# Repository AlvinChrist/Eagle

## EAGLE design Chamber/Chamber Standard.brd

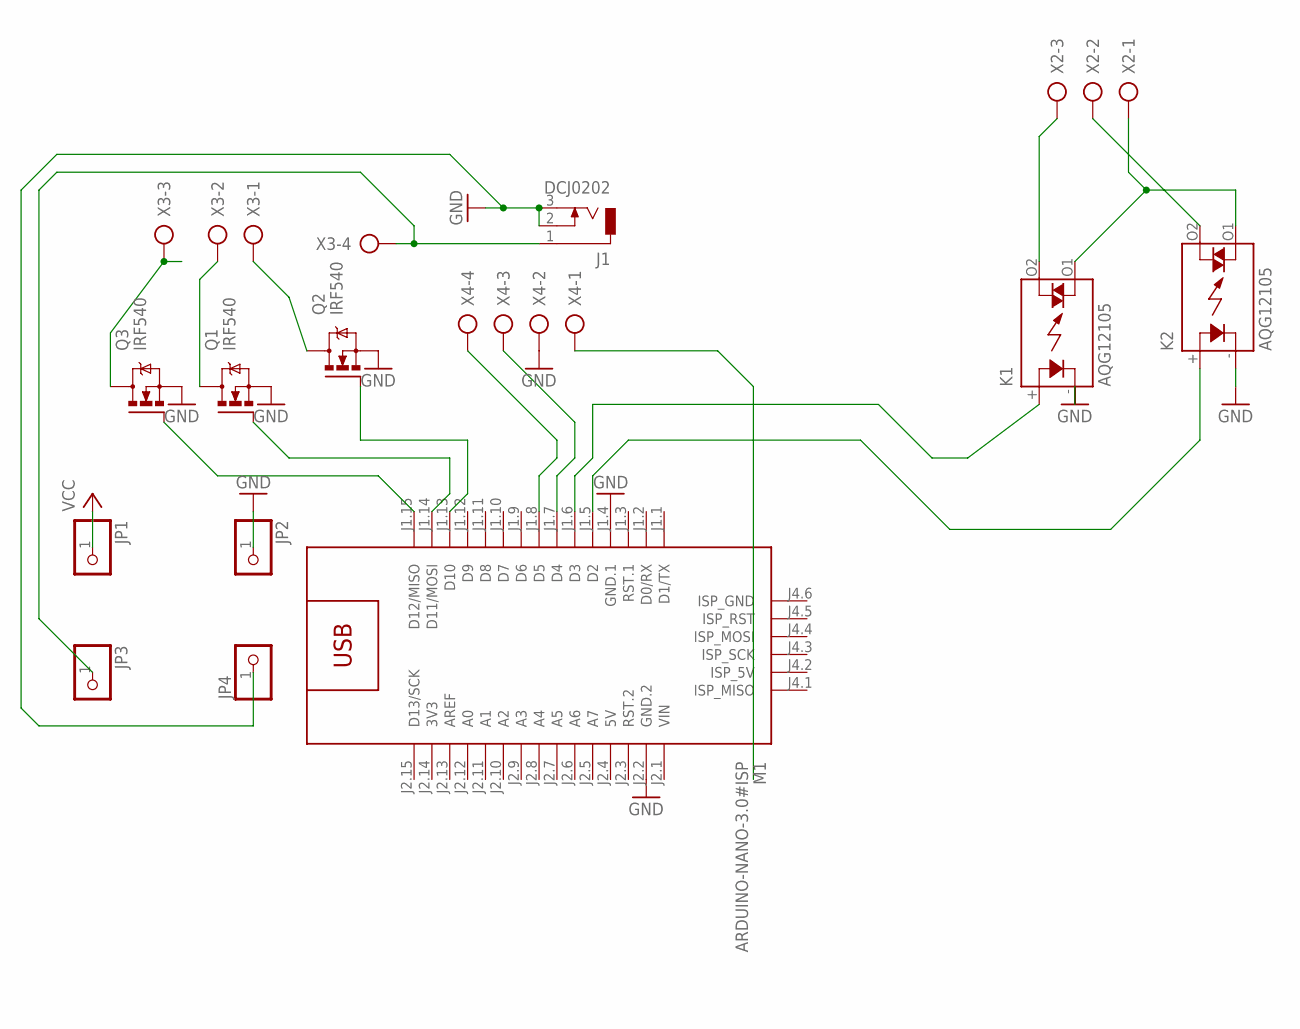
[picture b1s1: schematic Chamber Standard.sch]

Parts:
J1: DCJ0202
JP1, JP2, JP3, JP4: PINHD-1X1; 1X01
K1, K2: AQG12105; AQG
M1: ARDUINO-NANO-3.0#ISP
Q1, Q2, Q3: IRF540; TO220BV
X2: AK300/3
X3, X4: AK300/4

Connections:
3V3: M1.J2.14 (3V3)
5V: M1.J2.4 (5V), X4.1
12V: J1.1, JP3.1, X3.4
GND: J1.2, J1.3, JP2.1, JP4.1, K1.- (K), K2.- (K), Q1.S, Q2.S, Q3.S, X4.2
GND.1: M1.J2.2 (GND.2)
GND.2: M1.J1.4 (GND.1)
unnamed: M1.J1.13 (D10), Q2.G
unnamed: M1.J1.15 (D12/MISO), Q3.G
unnamed: K2.O2 (DS1), X2.2
unnamed: Q3.D, X3.3
unnamed: Q1.D, X3.2
unnamed: Q2.D, X3.1
unnamed: K1.+ (A), M1.J1.6 (D3)
unnamed: K2.+ (A), M1.J1.5 (D2)
unnamed: K1.O1 (DS2), K2.O1 (DS2), X2.1
unnamed: K1.O2 (DS1), X2.3
unnamed: M1.J1.7 (D4), X4.3
unnamed: M1.J1.8 (D5), X4.4
unnamed: M1.J1.14 (D11/MOSI), Q1.G
VCC: JP1.1
VIN: M1.J2.1 (VIN)

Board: 2 copper layers, 14 parts (0 on the bottom side), 16 nets, no tracks yet.

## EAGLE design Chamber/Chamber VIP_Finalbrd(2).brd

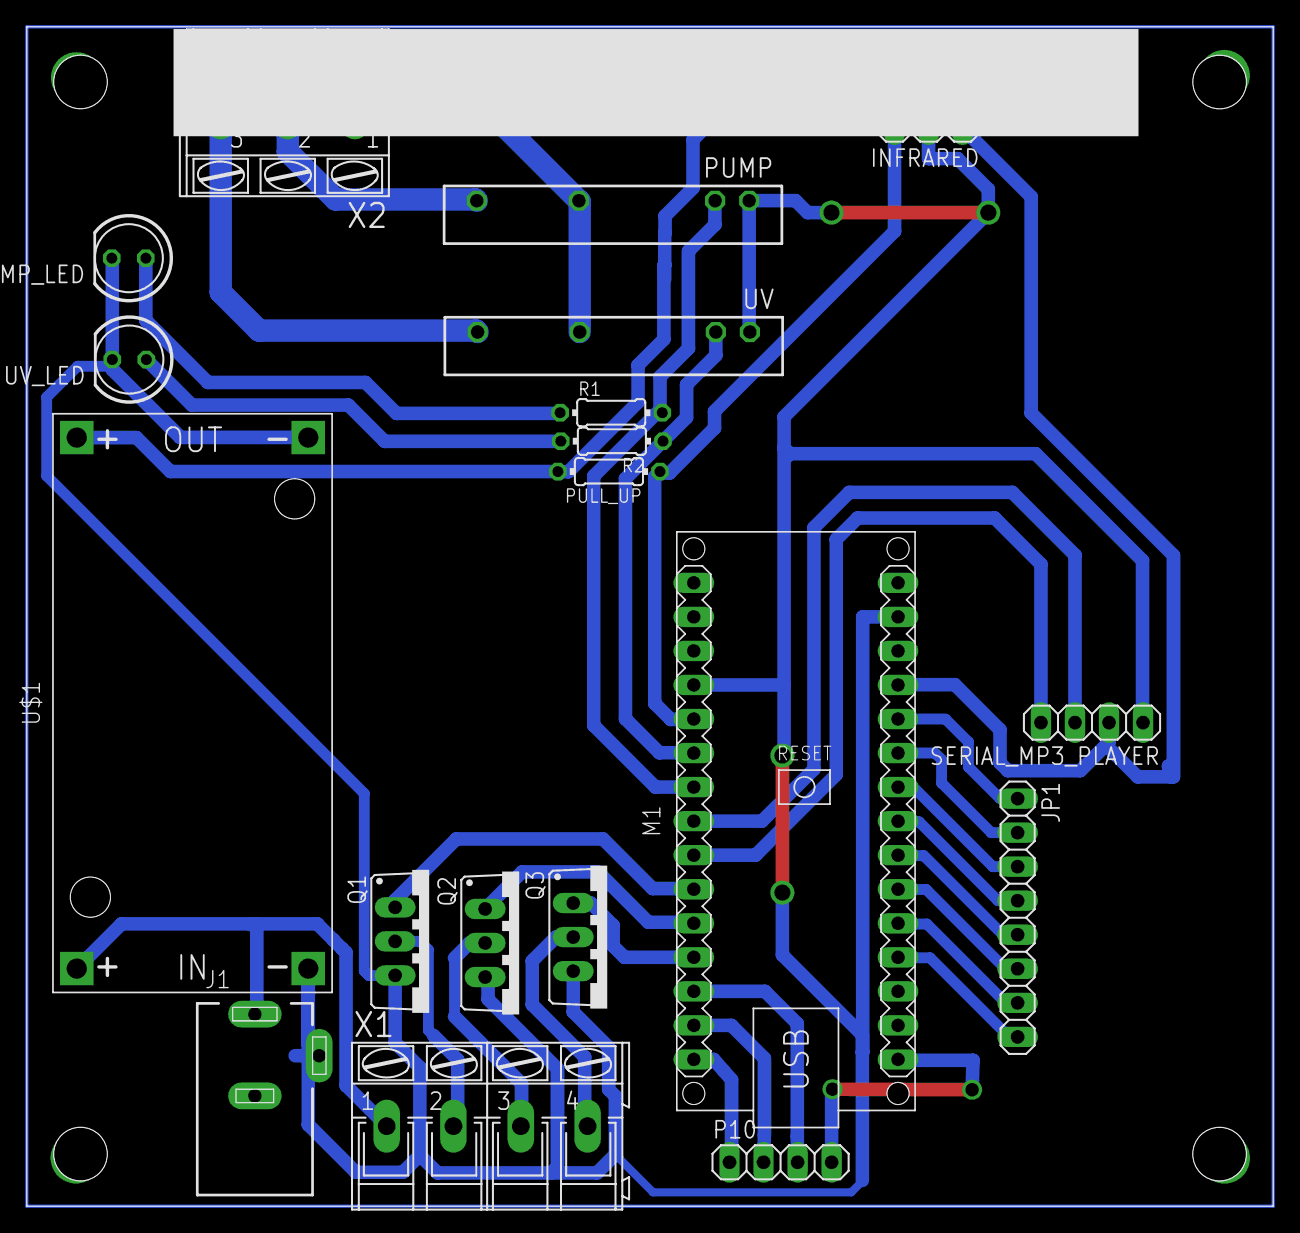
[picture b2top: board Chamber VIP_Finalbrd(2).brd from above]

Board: 2 copper layers, 93.0 x 88.0 mm, 19 parts (0 on the bottom side), 31 nets.

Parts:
INFRARED: 1X03
J1: DCJ0202
JP1: 1X08
M1: ARDUINO-NANO-3.0#ISP; ARDUINO-NANO-3.0
P10: 1X04
PULL_UP: 10k ohm; 0204/7
PUMP: AQG12105; AQG
PUMP_LED: LED5MM
Q1, Q2, Q3: IRF540; TO220BV
R1, R2: 1k ohm; 0204/7
SERIAL_MP3_PLAYER: 1X04
U$1: DC-DC-STEP-DOWN-LM2596
UV: AQG12105; AQG
UV_LED: LED5MM
X1: AK300/4
X2: AK300/3

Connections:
+5V: INFRARED.1, M1.J2.4, PULL_UP.2, SERIAL_MP3_PLAYER.2, U$1.OUT+
GND: INFRARED.2, J1.2, J1.3, M1.J1.4, M1.J2.2, PUMP.-, PUMP_LED.K, Q1.S, Q2.S, Q3.S, SERIAL_MP3_PLAYER.1, U$1.IN-, U$1.OUT-, UV.-, UV_LED.K
unnamed: Q3.D, X1.4
unnamed: J1.1, U$1.IN+, X1.1
unnamed: Q1.D, X1.2
unnamed: Q2.D, X1.3
unnamed: JP1.8, M1.J2.12
unnamed: PUMP.O2, X2.2
unnamed: M1.J1.12, Q3.G
unnamed: M1.J1.6, R2.1, UV.+
unnamed: M1.J1.10, Q1.G
unnamed: M1.J1.11, Q2.G
unnamed: M1.J1.9, SERIAL_MP3_PLAYER.4
unnamed: INFRARED.3, M1.J1.5, PULL_UP.1
unnamed: R2.2, UV_LED.A
unnamed: PUMP_LED.A, R1.1
unnamed: M1.J1.8, SERIAL_MP3_PLAYER.3
unnamed: M1.J1.7, PUMP.+, R1.2
unnamed: M1.J1.15, P10.1
unnamed: M1.J1.14, P10.2
unnamed: M1.J1.13, P10.3
unnamed: M1.J2.15, P10.4
unnamed: UV.O2, X2.3
unnamed: JP1.7, M1.J2.11
unnamed: JP1.6, M1.J2.10
unnamed: JP1.5, M1.J2.9
unnamed: JP1.4, M1.J2.8
unnamed: JP1.3, M1.J2.7
unnamed: JP1.2, M1.J2.6
unnamed: JP1.1, M1.J2.5
S$3: PUMP.O1, UV.O1, X2.1

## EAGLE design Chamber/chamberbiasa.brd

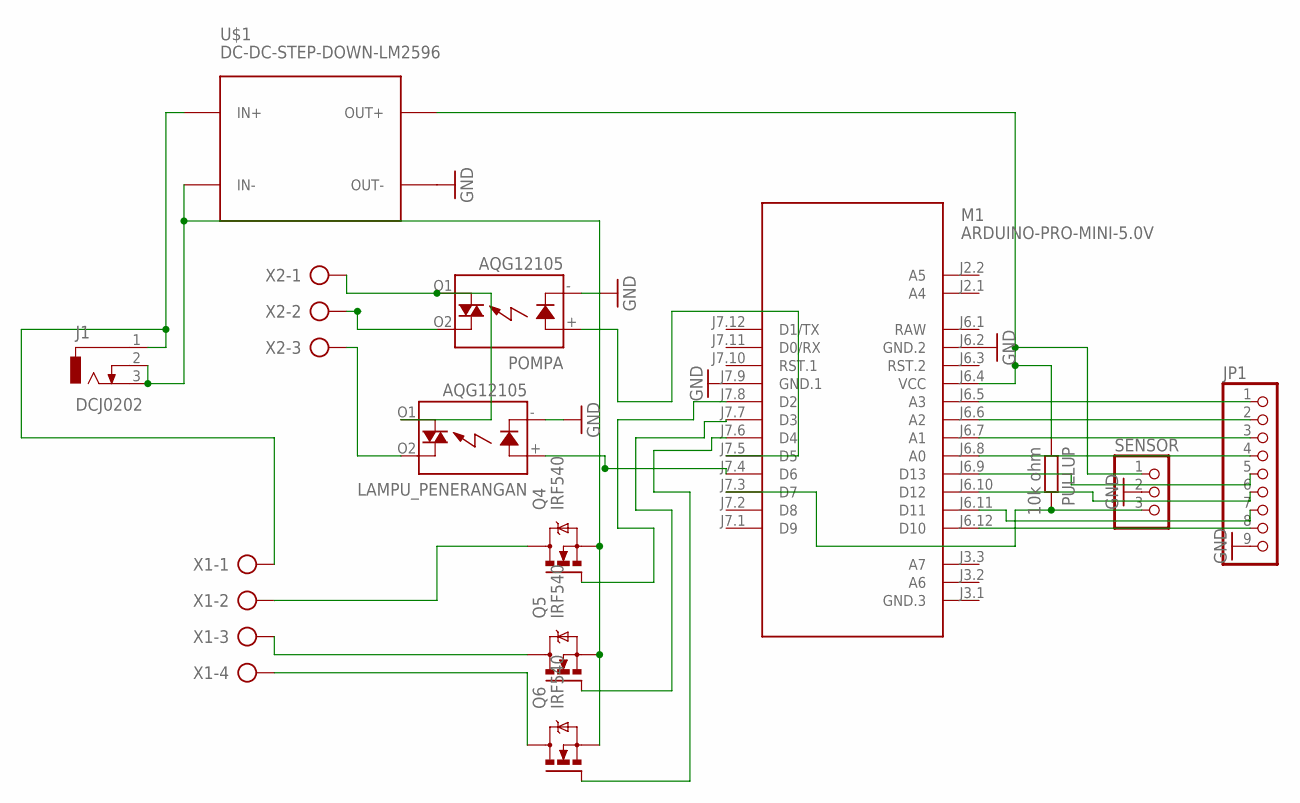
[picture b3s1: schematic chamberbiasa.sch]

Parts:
J1: DCJ0202
JP1: PINHD-1X9; 1X09
LAMPU_PENERANGAN: AQG12105; AQG
M1: ARDUINO-PRO-MINI-5.0V; ARDUINO-PRO-MINI
POMPA: AQG12105; AQG
PULLUP: 10k ohm; 0204/7
Q4, Q5, Q6: IRF540; TO220BV
SENSOR: PINHD-1X3; 1X03
U$1: DC-DC-STEP-DOWN-LM2596
X1: AK300/4
X2: AK300/3

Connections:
5V: M1.J6.4 (VCC), PULLUP.1, SENSOR.1, U$1.OUT+
-12V: J1.2, J1.3, Q4.S, Q5.S, Q6.S, U$1.IN-
GND: JP1.9, LAMPU_PENERANGAN.- (K), M1.J6.2 (GND.2), M1.J7.9 (GND.1), POMPA.- (K), SENSOR.2, U$1.OUT-
unnamed: LAMPU_PENERANGAN.+ (A), M1.J7.4 (D6)
unnamed: M1.J7.8 (D2), Q4.G
unnamed: M1.J7.5 (D5), POMPA.+ (A)
unnamed: M1.J7.7 (D3), Q5.G
unnamed: M1.J7.6 (D4), Q6.G
unnamed: Q4.D, X1.2
unnamed: Q5.D, X1.3
unnamed: Q6.D, X1.4
unnamed: J1.1, U$1.IN+, X1.1
unnamed: POMPA.O2 (DS1), X2.2
unnamed: LAMPU_PENERANGAN.O1 (DS2), POMPA.O1 (DS2), X2.1
unnamed: LAMPU_PENERANGAN.O2 (DS1), X2.3
unnamed: JP1.1, M1.J6.5 (A3)
unnamed: M1.J7.3 (D7), PULLUP.2, SENSOR.3
unnamed: JP1.2, M1.J6.6 (A2)
unnamed: JP1.3, M1.J6.7 (A1)
unnamed: JP1.4, M1.J6.8 (A0)
unnamed: JP1.5, M1.J6.9 (D13)
unnamed: JP1.6, M1.J6.10 (D12)
unnamed: JP1.7, M1.J6.11 (D11)
unnamed: JP1.8, M1.J6.12 (D10)
RAW: M1.J6.1 (RAW)

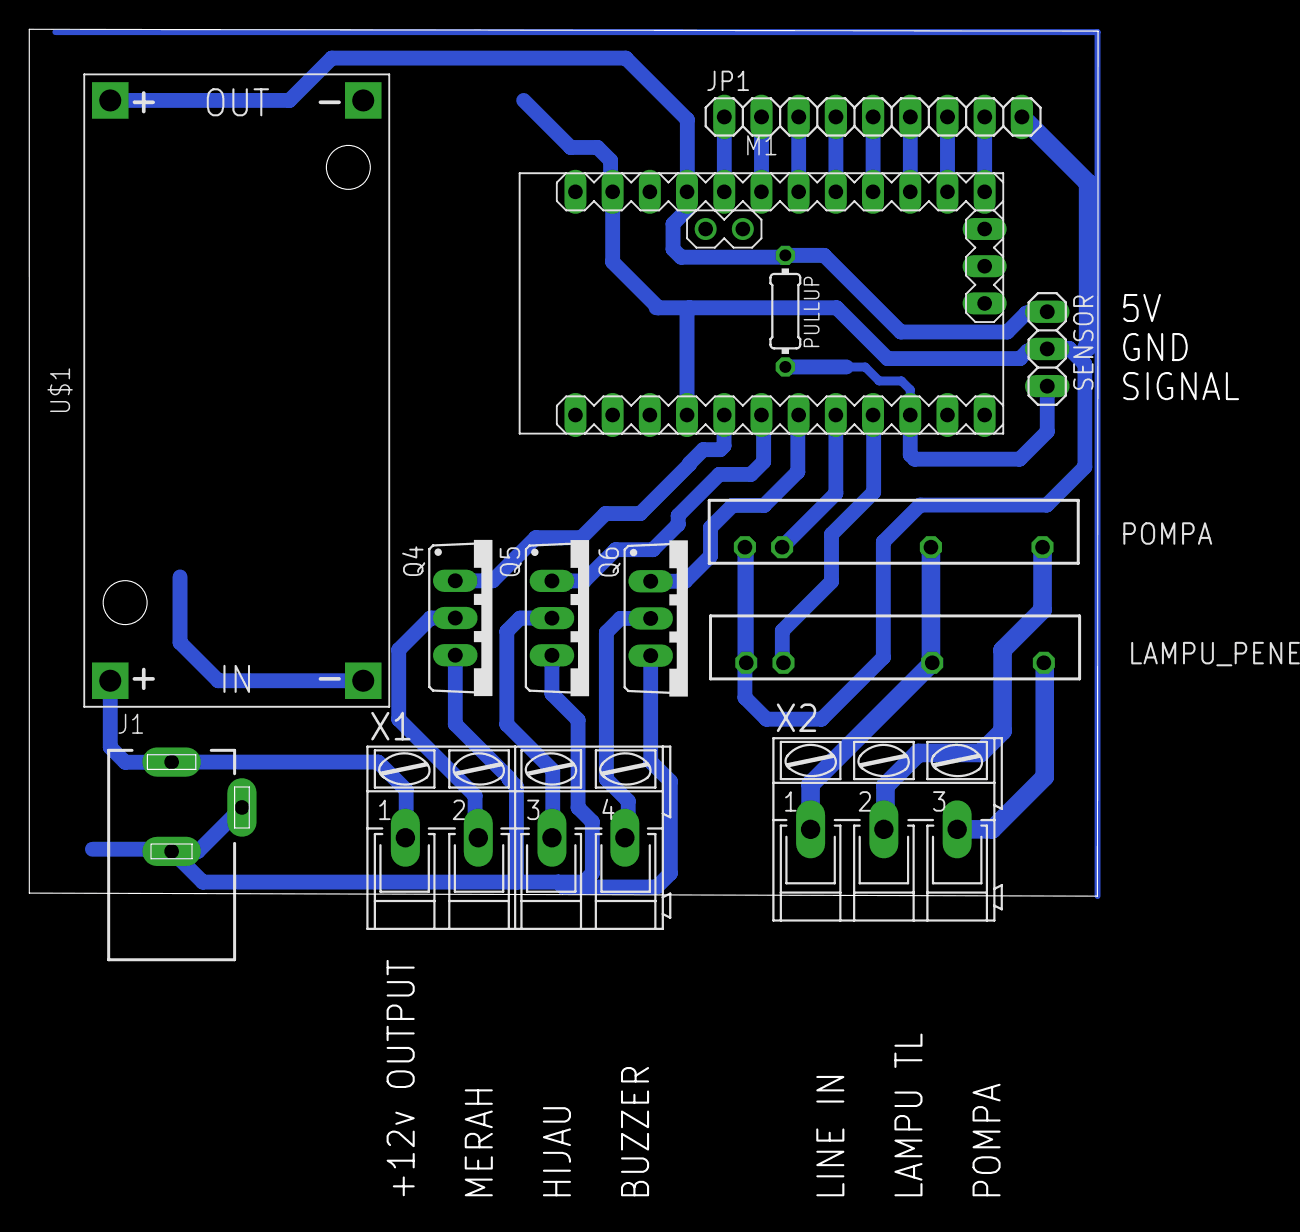
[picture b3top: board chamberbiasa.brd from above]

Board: 2 copper layers, 73.0 x 59.2 mm, 13 parts (0 on the bottom side), 24 nets.

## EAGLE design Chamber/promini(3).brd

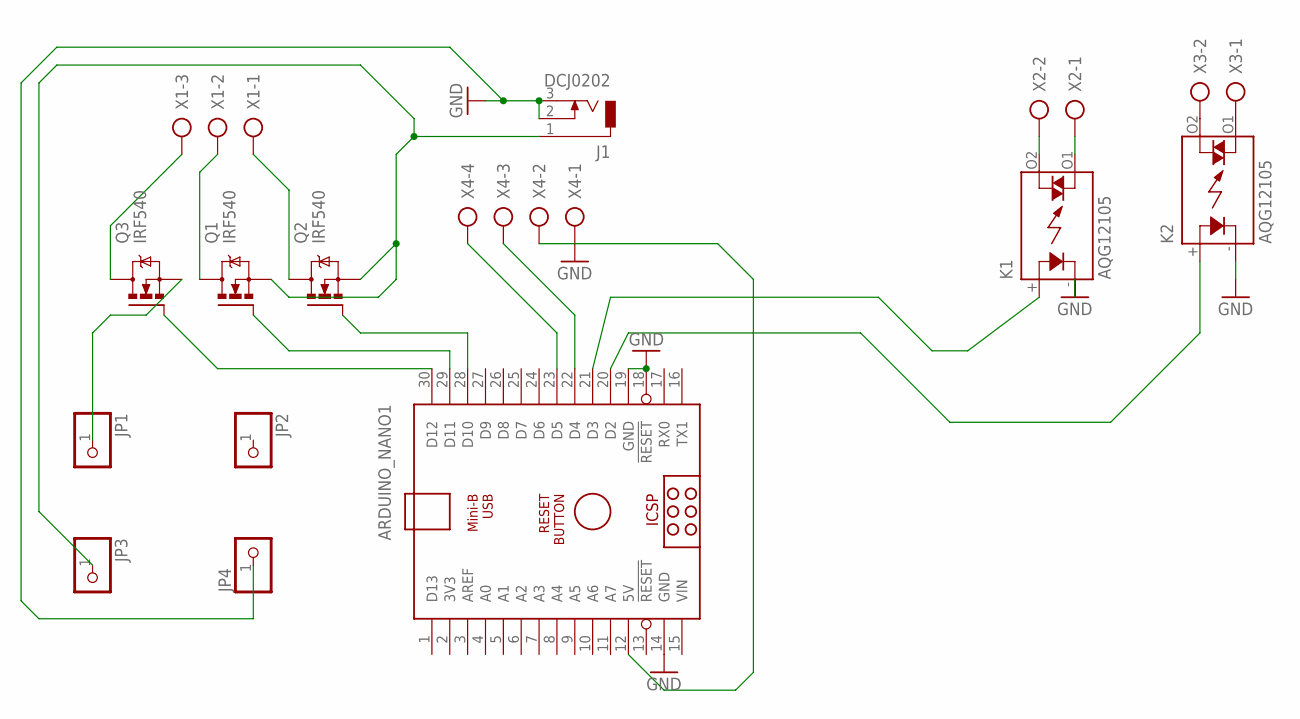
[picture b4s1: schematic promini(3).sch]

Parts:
ARDUINO_NANO1: ARDUINO_NANO
J1: DCJ0202
JP1, JP2, JP3, JP4: PINHD-1X1; 1X01
K1, K2: AQG12105; AQG
Q1, Q2, Q3: IRF540; TO220BV
X1: AK300/3
X2, X3: AK300/2
X4: AK300/4

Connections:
5V: ARDUINO_NANO1.12 (5V), X4.2
12V: J1.1, JP3.1, Q1.S, Q2.S
GND: ARDUINO_NANO1.14 (GND), ARDUINO_NANO1.18 (!RESET), ARDUINO_NANO1.19 (GND), J1.2, J1.3, JP4.1, K1.- (K), K2.- (K), X4.1
unnamed: ARDUINO_NANO1.28 (D10), Q2.G
unnamed: ARDUINO_NANO1.30 (D12), Q3.G
unnamed: JP1.1, Q3.S
unnamed: Q3.D, X1.3
unnamed: Q1.D, X1.2
unnamed: Q2.D, X1.1
unnamed: ARDUINO_NANO1.21 (D3), K1.+ (A)
unnamed: ARDUINO_NANO1.20 (D2), K2.+ (A)
unnamed: K1.O1 (DS2), X2.1
unnamed: K1.O2 (DS1), X2.2
unnamed: K2.O1 (DS2), X3.1
unnamed: K2.O2 (DS1), X3.2
unnamed: ARDUINO_NANO1.22 (D4), X4.3
unnamed: ARDUINO_NANO1.23 (D5), X4.4
unnamed: ARDUINO_NANO1.29 (D11), Q1.G
VIN: ARDUINO_NANO1.15 (VIN)

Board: 2 copper layers, 15 parts (0 on the bottom side), 18 nets, no tracks yet.

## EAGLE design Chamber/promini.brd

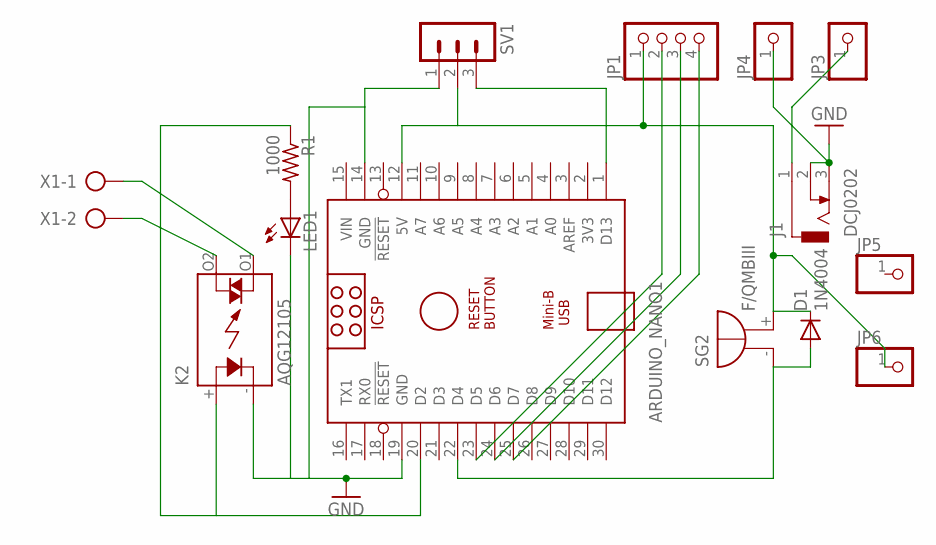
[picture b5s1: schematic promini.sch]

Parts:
ARDUINO_NANO1: ARDUINO_NANO
D1: 1N4004; DO41-10
J1: DCJ0202
JP1: PINHD-1X4; 1X04
JP3, JP4, JP5, JP6: PINHD-1X1; 1X01
K2: AQG12105; AQG
LED1: LED5MM
R1: 1000; 0204/7
SG2: F/QMBIII
SV1: MA03-1
X1: AK300/2

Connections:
5V: ARDUINO_NANO1.12 (5V), D1.C, JP1.1, JP6.1, SG2.+ (-), SV1.2
D2: ARDUINO_NANO1.20 (D2), K2.+ (A), R1.1
D4: ARDUINO_NANO1.22 (D4), D1.A, SG2.- (+)
D13: ARDUINO_NANO1.1 (D13), SV1.3
GND: ARDUINO_NANO1.14 (GND), ARDUINO_NANO1.19 (GND), J1.2, J1.3, JP4.1, K2.- (K), LED1.K (C), SV1.1
unnamed: K2.O2 (DS1), X1.2
unnamed: K2.O1 (DS2), X1.1
unnamed: ARDUINO_NANO1.23 (D5), JP1.2
unnamed: LED1.A, R1.2
unnamed: J1.1, JP3.1
unnamed: ARDUINO_NANO1.24 (D6), JP1.3
unnamed: ARDUINO_NANO1.25 (D7), JP1.4
VIN: ARDUINO_NANO1.15 (VIN)

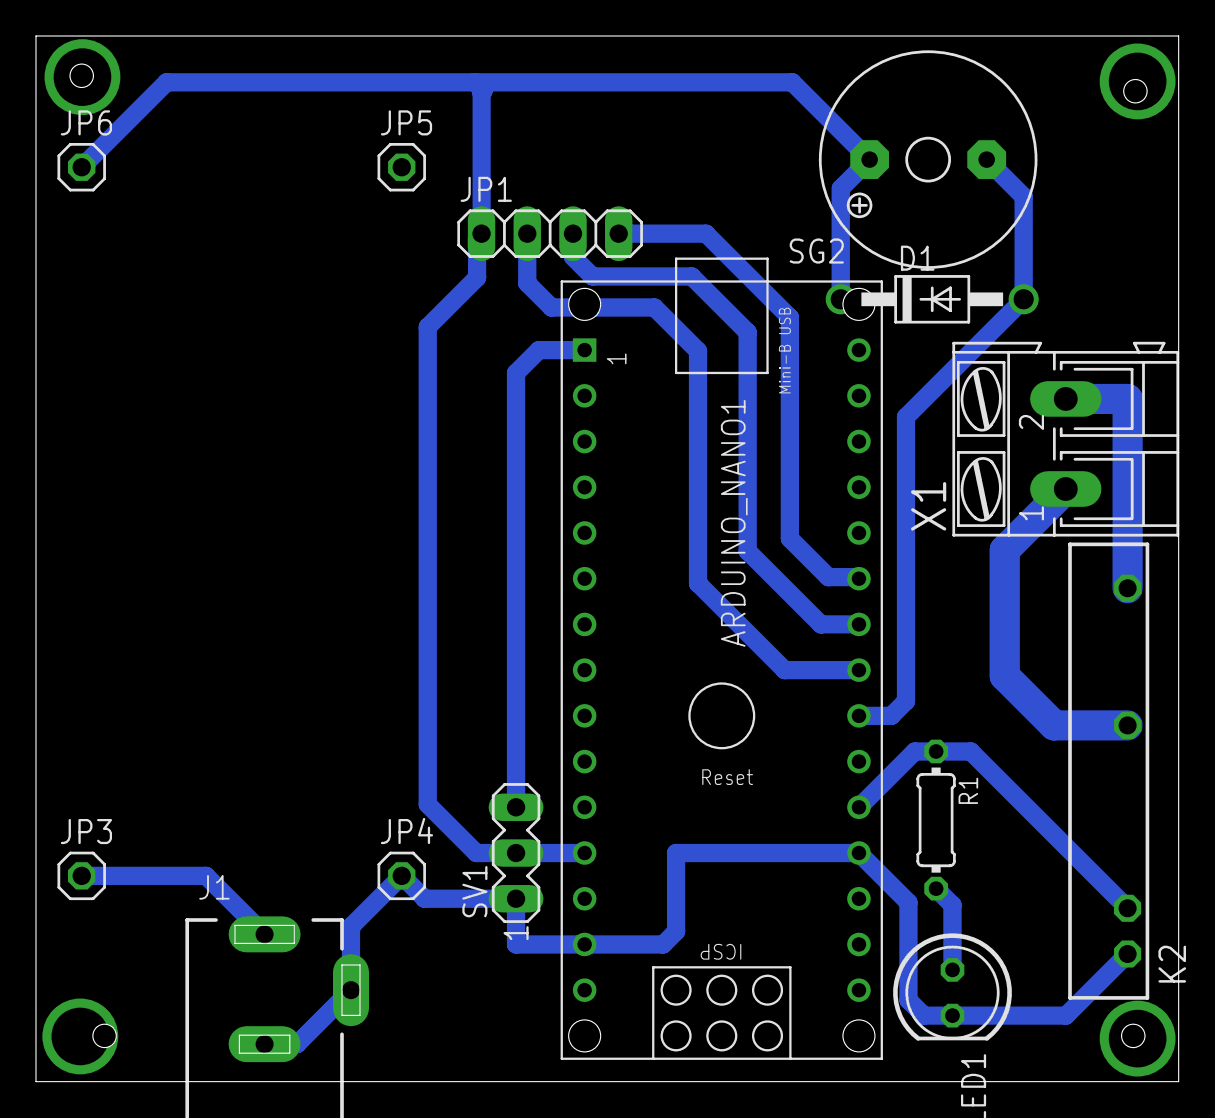
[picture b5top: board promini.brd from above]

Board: 2 copper layers, 63.5 x 58.1 mm, 14 parts (0 on the bottom side), 12 nets.

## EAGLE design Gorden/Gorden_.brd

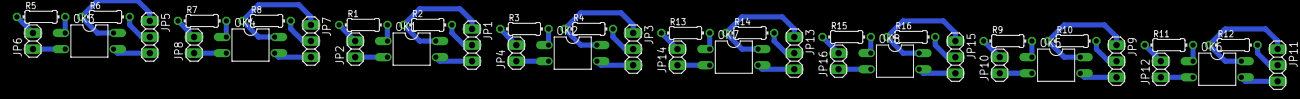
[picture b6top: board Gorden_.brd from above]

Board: 2 copper layers, 40 parts (0 on the bottom side), 48 nets.

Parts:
JP1, JP3, JP5, JP7, JP9, JP11, JP13, JP15: 1X03
JP2, JP4, JP6, JP8, JP10, JP12, JP14, JP16: 1X02
OK1, OK2, OK3, OK4, OK5, OK6, OK7, OK8: PC817; DIL04
R1, R2, R3, R4, R5, R6, R7, R8, R9, R10, R11, R12, R13, R14, R15, R16: 0204/7

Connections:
unnamed: JP1.3, OK1.3
unnamed: OK1.1, R1.2
unnamed: JP1.1, OK1.4, R2.1
unnamed: JP1.2, R2.2
unnamed: JP2.2, R1.1
unnamed: JP2.1, OK1.2
unnamed: OK2.1, R3.2
unnamed: JP3.3, OK2.3
unnamed: JP3.1, OK2.4, R4.1
unnamed: JP3.2, R4.2
unnamed: JP4.2, R3.1
unnamed: JP4.1, OK2.2
unnamed: OK3.1, R5.2
unnamed: JP5.3, OK3.3
unnamed: JP5.1, OK3.4, R6.1
unnamed: JP5.2, R6.2
unnamed: JP6.2, R5.1
unnamed: JP6.1, OK3.2
unnamed: OK4.1, R7.2
unnamed: JP7.3, OK4.3
unnamed: JP7.1, OK4.4, R8.1
unnamed: JP7.2, R8.2
unnamed: JP8.2, R7.1
unnamed: JP8.1, OK4.2
unnamed: OK5.1, R9.2
unnamed: JP9.3, OK5.3
unnamed: JP9.1, OK5.4, R10.1
unnamed: JP9.2, R10.2
unnamed: JP10.2, R9.1
unnamed: JP10.1, OK5.2
unnamed: OK6.1, R11.2
unnamed: JP11.3, OK6.3
unnamed: JP11.1, OK6.4, R12.1
unnamed: JP11.2, R12.2
unnamed: JP12.2, R11.1
unnamed: JP12.1, OK6.2
unnamed: OK7.1, R13.2
unnamed: JP13.3, OK7.3
unnamed: JP13.1, OK7.4, R14.1
unnamed: JP13.2, R14.2
unnamed: JP14.2, R13.1
unnamed: JP14.1, OK7.2
unnamed: OK8.1, R15.2
unnamed: JP15.3, OK8.3
unnamed: JP15.1, OK8.4, R16.1
unnamed: JP15.2, R16.2
unnamed: JP16.2, R15.1
unnamed: JP16.1, OK8.2

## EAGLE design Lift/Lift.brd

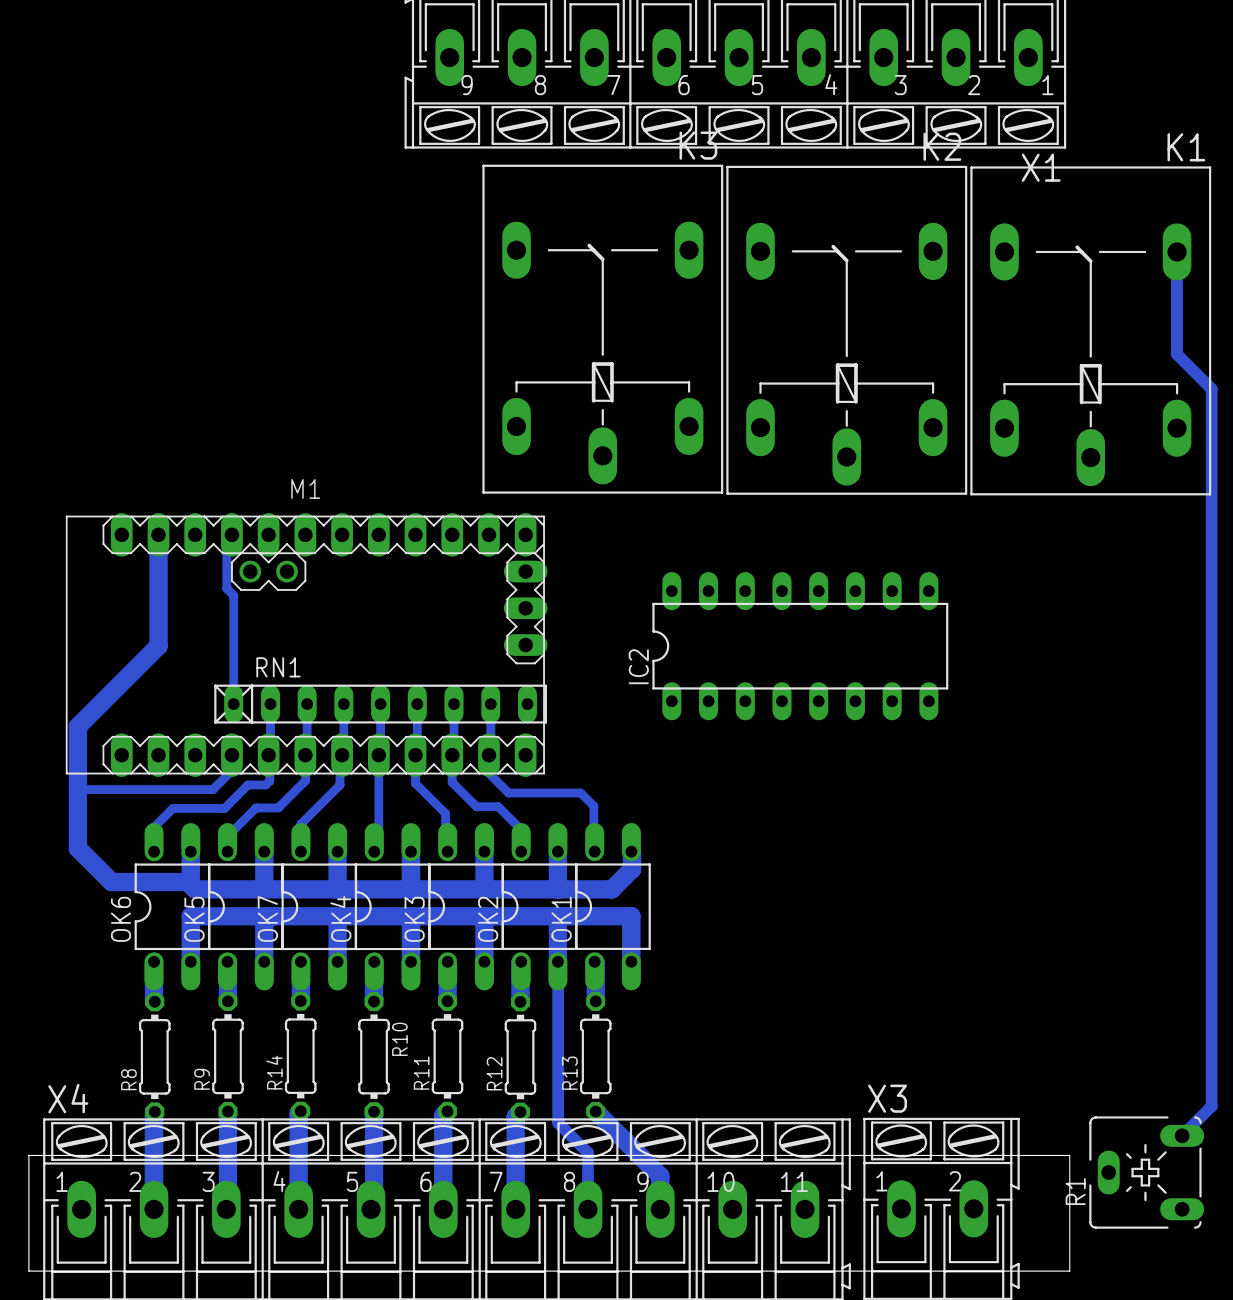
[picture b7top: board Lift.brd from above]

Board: 2 copper layers, 24 parts (0 on the bottom side), 41 nets.

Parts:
IC2: ULN2003AN; DIL16
K1, K2, K3: G5L; G5LE
M1: ARDUINO-PRO-MINI-5.0V; ARDUINO-PRO-MINI
OK1, OK2, OK3, OK4, OK5, OK6, OK7: PC817; DIL04
R1: CA6V
R8, R9, R10, R11, R12, R13, R14: 0204/7
RN1: RN-9
X1: AK300/9
X3: AK300/2
X4: AK300/11

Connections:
5V: K1.S, R1.E, X4.10
12V: IC2.9, K1.1, K2.1, K3.1, X3.2
24V: K2.P, K3.P, X1.9, X4.1
GND1: R1.A, X4.11
GND2: OK1.2, OK2.2, OK3.2, OK4.2, OK5.2, OK6.2, OK7.2, X4.8
GND3: IC2.8, X3.1
unnamed: OK2.1, R12.2
unnamed: OK1.1, R13.2
unnamed: OK3.1, R11.2
unnamed: R10.2, X4.5
unnamed: OK7.1, R14.2
unnamed: R14.1, X4.4
unnamed: IC2.10, K1.2
unnamed: M1.J7.7, OK5.4, RN1.3
unnamed: M1.J7.5, OK4.4, RN1.5
unnamed: M1.J7.4, OK3.4, RN1.6
unnamed: K1.O, R1.S
unnamed: M1.J7.6, OK7.4, RN1.4
unnamed: M1.J6.4, RN1.1
unnamed: K1.P, X1.1
unnamed: R8.1, X4.2
unnamed: R9.1, X4.3
unnamed: R11.1, X4.6
unnamed: M1.J7.3, OK2.4, RN1.7
unnamed: OK5.1, R9.2
unnamed: R13.1, X4.9
unnamed: M1.J6.2, M1.J7.9, OK1.3, OK2.3, OK3.3, OK4.3, OK5.3, OK6.3, OK7.3
unnamed: IC2.12, K3.2
unnamed: R12.1, X4.7
unnamed: M1.J7.2, OK1.4, RN1.8
unnamed: IC2.7, M1.J7.1
unnamed: IC2.11, K2.2
unnamed: K3.S, X1.4
unnamed: X1.7, X1.8
unnamed: X1.5, X1.6
unnamed: K2.S, X1.3
unnamed: M1.J7.8, OK6.4, RN1.2
unnamed: OK6.1, R8.2
unnamed: OK4.1, R10.1
unnamed: IC2.5, M1.J6.11
unnamed: IC2.6, M1.J6.12

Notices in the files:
parts and their libraries:
diy-modules: Released under the Creative Commons Attribution 4.0 International License: http://creativecommons.org/licenses/by/4.0
